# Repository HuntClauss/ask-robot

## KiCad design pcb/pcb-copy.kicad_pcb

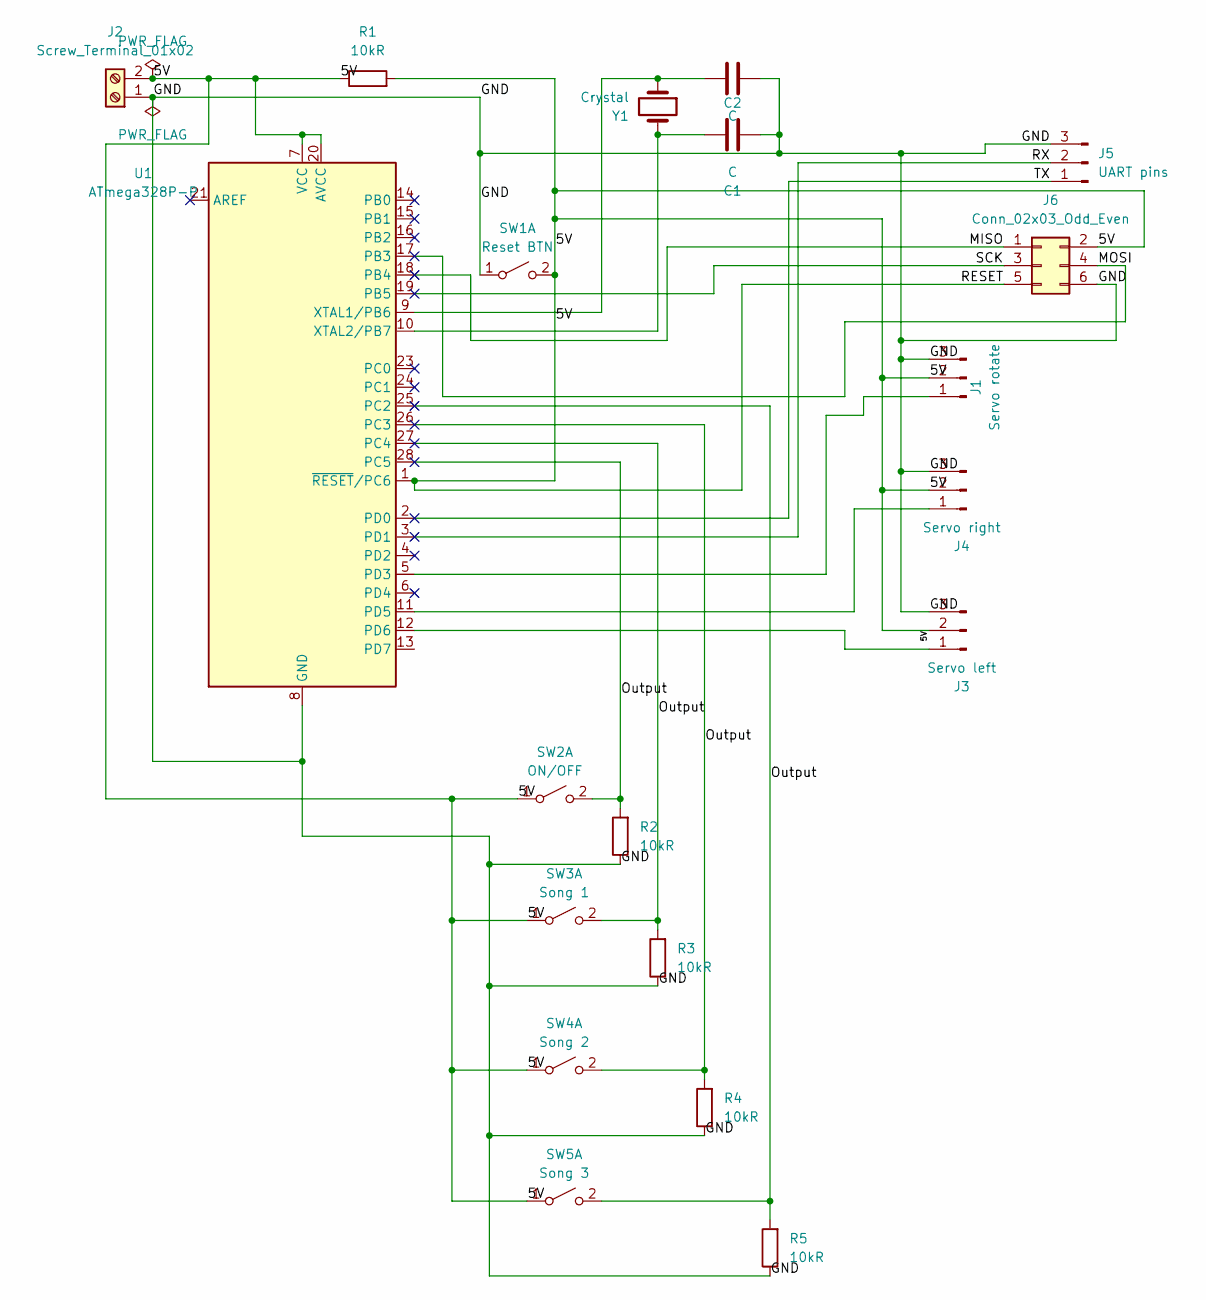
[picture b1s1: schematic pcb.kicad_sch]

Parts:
C1, C2: C; C_Disc_D3.0mm_W2.0mm_P2.50mm
J1: Servo rotate; PinHeader_1x03_P2.54mm_Vertical
J2: Screw_Terminal_01x02; TerminalBlock_Phoenix_MKDS-1,5-2_1x02_P5.00mm_Horizontal
J3: Servo left; PinHeader_1x03_P2.54mm_Vertical
J4: Servo right; PinHeader_1x03_P2.54mm_Vertical
J5: UART pins; PinHeader_1x03_P2.54mm_Vertical
J6: Conn_02x03_Odd_Even; PinHeader_2x03_P2.54mm_Vertical
R1, R2, R3, R4, R5: 10kR; R_Axial_DIN0204_L3.6mm_D1.6mm_P1.90mm_Vertical
SW1: Reset BTN; SW_PUSH_6mm_H7.3mm
SW2: ON/OFF; SW_PUSH_6mm_H7.3mm
SW3: Song 1; SW_PUSH_6mm_H7.3mm
SW4: Song 2; SW_PUSH_6mm_H7.3mm
SW5: Song 3; SW_PUSH_6mm_H7.3mm
U1: ATmega328P-P; DIP-28_W7.62mm_Socket
Y1: Crystal; Crystal_HC49-4H_Vertical

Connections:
/5V: J1.2, J2.2, J3.2, J4.2, J6.2, J6.5, R1.1, R1.2, SW1.2 (B), SW2.1 (A), SW3.1 (A), SW4.1 (A), SW5.1 (A), U1.1 (~RESET/PC6), U1.7 (VCC), U1.20 (AVCC)
/GND: C1.1, C2.1, J1.3, J2.1, J3.3, J4.3, J5.3, J6.6, R2.1, R3.1, R4.1, R5.1, SW1.1 (A), U1.8 (GND), U1.22 (GND)
/MISO: J6.1, U1.18 (PB4)
/MOSI: J6.4, U1.17 (PB3)
/Output: R2.2, R3.2, R4.2, R5.2, SW2.2 (B), SW3.2 (B), SW4.2 (B), SW5.2 (B), U1.25 (PC2), U1.26 (PC3), U1.27 (PC4), U1.28 (PC5)
/RX: J5.2, U1.3 (PD1)
/SCK: J6.3, U1.19 (PB5)
/TX: J5.1, U1.2 (PD0)
unnamed: J1.1, U1.5 (PD3)
unnamed: J3.1, U1.12 (PD6)
unnamed: J4.1, U1.11 (PD5)
unnamed: C2.2, U1.9 (XTAL1/PB6), Y1.1
unnamed: C1.2, U1.10 (XTAL2/PB7), Y1.2

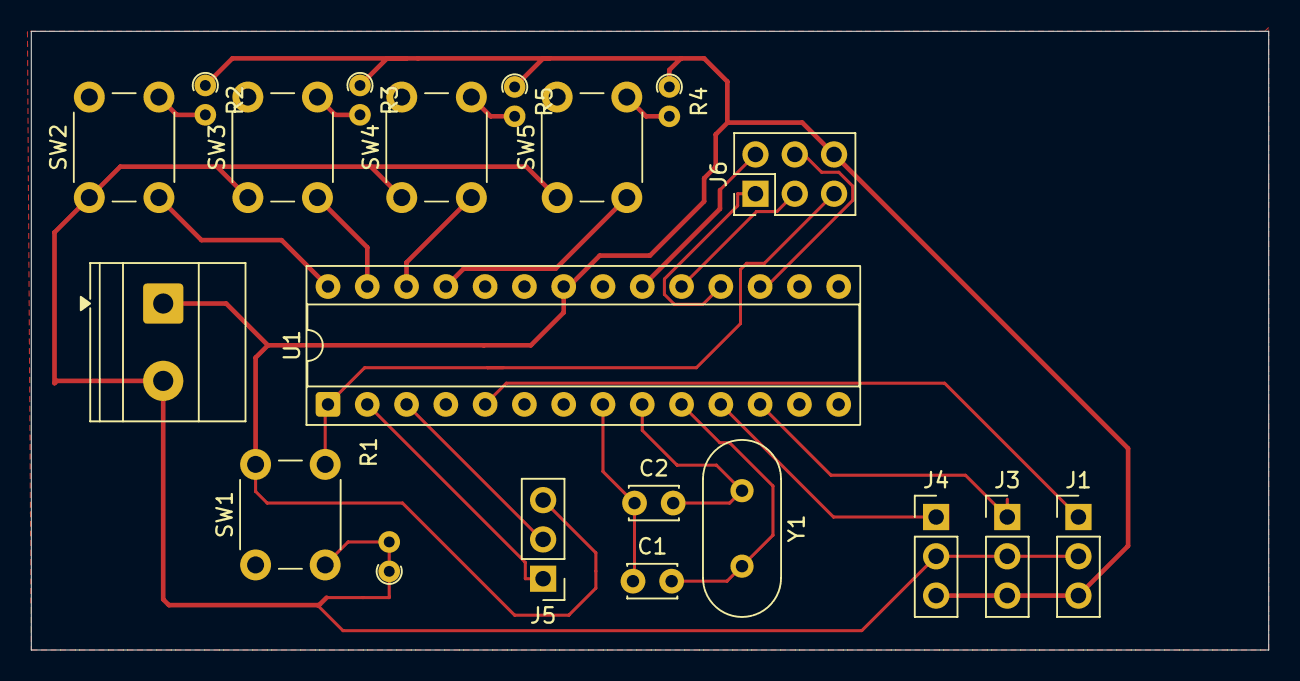
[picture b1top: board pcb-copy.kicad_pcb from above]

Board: 2 copper layers, 80.0 x 40.0 mm, 20 parts (0 on the bottom side), 13 nets.

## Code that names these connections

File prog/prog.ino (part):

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
// #define SERVO_LEFT_PIN PIN_PB1
// #define SERVO_RIGHT_PIN PIN_PB2
// #define SERVO_ROTATE_PIN PIN_PB3

// #define BUTTON_TOGGLE A5
// #define RESET_BUTTON A4
// #define TEST_BUTTON A3

#define SERVO_LEFT_PIN PIN_PD6
#define SERVO_RIGHT_PIN PIN_PD5
#define SERVO_ROTATE_PIN PIN_PD3

// ================================================

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
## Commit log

2025-05-18 init commit
2025-05-18 feat: accept numvers as notes
